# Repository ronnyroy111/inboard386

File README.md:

# Intel Inboard 386/PC Clone
https://forum.vcfed.org/index.php?threads/inboard386-pc-clone.1257894/
https://forum.theretroweb.com/t/intel-inboard-386-pc-accelerator-clone/44

This is a complete reverse engineered reproduction of [Intel Inboard 386/PC Accelerator Card](https://theretroweb.com/expansioncards/s/intel-inboard-386-pc).  
It's based on a damaged card that i obtained a while ago and managed to fix but decided to sacrifice for a reproduction.  
The Inboard 386/PC is an upgrade card from Intel for the IBM PC/XT and clones that upgraded the 8088 CPU to a 16MHz 386DX and up to 5MB of system memory.  
The card only uses standard 74 series logic chips along with some PALs/PROMs that were luckily not secured and were successfully dumped.  
The PCB is a 6 layer design with 4 signal layers. To aid with reverse engineering it i ended up choosing the destructive route and sanded the entire PCB down to the inner layers.  
By now the PCB design has been completed while the schematic still needs cleanup and further reverse engineering of the programmable logic to completely understand.  

The first revision of the board has been tested and confirmed to be working.  
  
Dumps of the PAL Chips and CUPL equations for the replacement Atmel PLD chips are in /logic.  
A memory expansion board prototype can be found under /mem.  
A 3D model of the bracket is at /bracket.  

The original board never intended for more than 5MB of ram to be used but can be modified with updated Logic equations in U71 to theoretically use up to 16MB.  
However the Inboard maps the portion of memory used for ROM caching at 0x580000-5FFFFF which is expected by INBRDPS.SYS.  
Currently that limits >5MB of memory to not use caching but could probably be solved with a modified INBRDPS.SYS.  

This current board design is a 1:1 copy of the original PCB, excluding some small details.  
A more compact version utilising SIMM memory and CPLDs is currently in work.  

# Assembly Guide:
You need the PCB for the inboard as well as the PROM adapter.  
A list of all required other components is located at /inboard386/parts_list.xlsx  
An html BOM is at /inboard386/bom/ibom.html  
The ideal assembly order is to place the small decoupling caps and resistors first, then place the chips and finish with the sockets, headers and large capacitor.  
For bending the capacitors/resistors one of these guides is very useful https://www.thingiverse.com/thing:168412

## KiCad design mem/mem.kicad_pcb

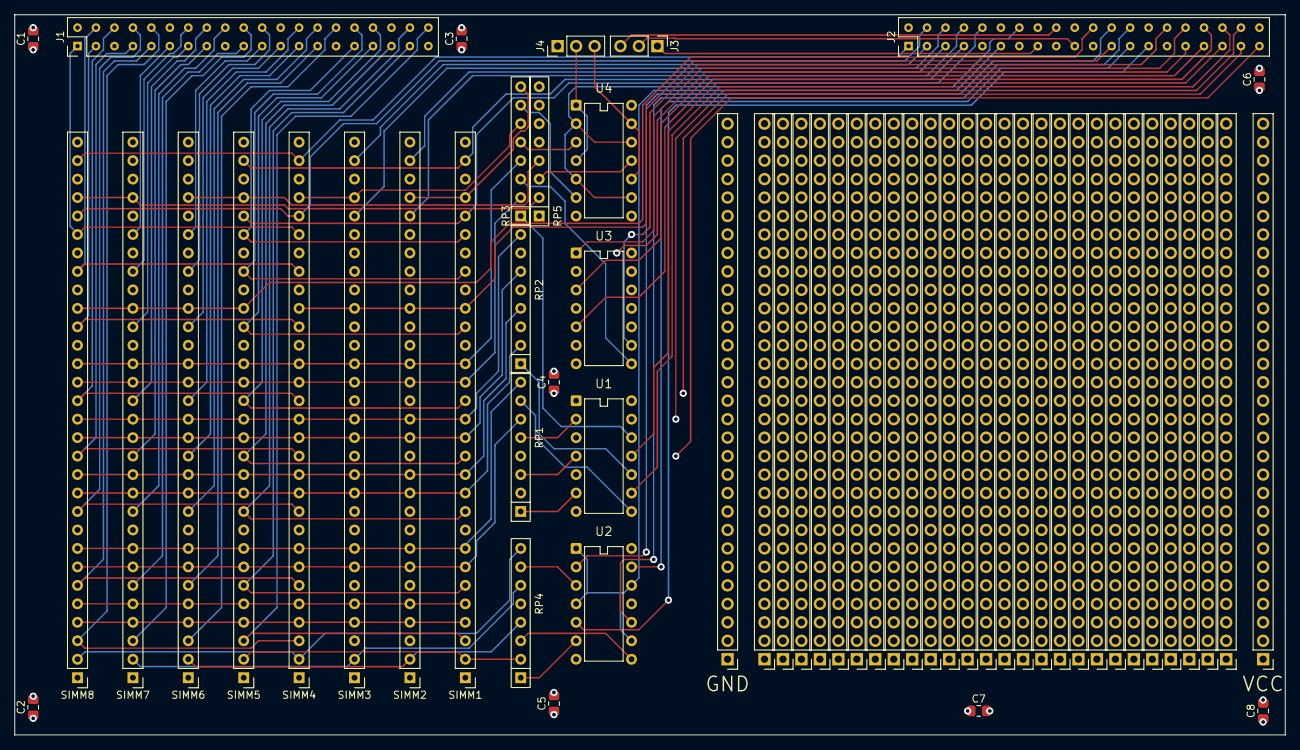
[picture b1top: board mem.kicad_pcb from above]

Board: 4 copper layers, 174.8 x 99.1 mm, 57 parts (0 on the bottom side), 101 nets.

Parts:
C1, C2, C3, C4, C5, C6, C7, C8: 100nF; C_0805_2012Metric_Pad1.18x1.45mm_HandSolder
J1, J2: Conn_02x20_Odd_Even; PinHeader_2x20_P2.54mm_inboard_mem
J3, J4: Conn_01x03_Pin; PinHeader_1x03_P2.54mm_Vertical
J5, J6, J7, J8, J9, J10, J11, J12, J13, J14, J15, J16, J17, J18, J19, J20, J21, J22, J23, J24, J25, J26, J27, J28, J29, J30, J31, J32: Conn_01x30; PinHeader_1x30_P2.54mm_Vertical
RP1, RP2, RP3, RP4, RP5: 22; R_Array_SIP8_layer
SIMM1, SIMM2, SIMM3, SIMM4, SIMM5, SIMM6, SIMM7, SIMM8: SIMM30; PinHeader_1x30_P2.54mm_Vertical_layer
U1, U3: 74AS1004; DIP-14_W7.62mm_layer
U2, U4: 742S1032; DIP-14_W7.62mm_layer

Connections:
+5V: C1.2, C2.2, C3.2, C4.2, C5.2, C6.2, C7.2, C8.2, J1.5, J1.17, J1.29, J1.39, J2.9, J2.13, J2.17, J2.21, J2.29, J30.1, J30.2, J30.3, J30.4, J30.5, J30.6, J30.7, J30.8, J30.9, J30.10, J30.11, J30.12, J30.13, J30.14, J30.15, J30.16, J30.17, J30.18, J30.19, J30.20, J30.21, J30.22, J30.23, J30.24, J30.25, J30.26, J30.27, J30.28, J30.29, J30.30, SIMM1.1 (VCC), SIMM1.30 (VCC), SIMM2.1 (VCC), SIMM2.30 (VCC), SIMM3.1 (VCC), SIMM3.30 (VCC), SIMM4.1 (VCC), SIMM4.30 (VCC), SIMM5.1 (VCC), SIMM5.30 (VCC), SIMM6.1 (VCC), SIMM6.30 (VCC), SIMM7.1 (VCC), SIMM7.30 (VCC), SIMM8.1 (VCC), SIMM8.30 (VCC), U1.14 (VCC), U2.14 (VCC), U3.14 (VCC), U4.14 (VCC)
/RAS_1M: J2.15, J3.1
/RAS_256K_1: J2.19, J3.2
/RAS_256K_2: J2.18, J3.3
GND: C1.1, C2.1, C3.1, C4.1, C5.1, C6.1, C7.1, C8.1, J1.2, J1.12, J1.24, J1.36, J2.2, J2.12, J2.16, J2.20, J2.28, J2.40, J29.1, J29.2, J29.3, J29.4, J29.5, J29.6, J29.7, J29.8, J29.9, J29.10, J29.11, J29.12, J29.13, J29.14, J29.15, J29.16, J29.17, J29.18, J29.19, J29.20, J29.21, J29.22, J29.23, J29.24, J29.25, J29.26, J29.27, J29.28, J29.29, J29.30, SIMM1.9 (GND), SIMM1.22 (GND), SIMM2.9 (GND), SIMM2.22 (GND), SIMM3.9 (GND), SIMM3.22 (GND), SIMM4.9 (GND), SIMM4.22 (GND), SIMM5.9 (GND), SIMM5.22 (GND), SIMM6.9 (GND), SIMM6.22 (GND), SIMM7.9 (GND), SIMM7.22 (GND), SIMM8.9 (GND), SIMM8.22 (GND), U1.7 (GND), U2.7 (GND), U3.7 (GND), U4.7 (GND)
MA0: RP1.2 (R1.2), SIMM1.4 (A0), SIMM2.4 (A0), SIMM3.4 (A0), SIMM4.4 (A0), SIMM5.4 (A0), SIMM6.4 (A0), SIMM7.4 (A0), SIMM8.4 (A0)
MA1: RP1.4 (R2.2), SIMM1.5 (A1), SIMM2.5 (A1), SIMM3.5 (A1), SIMM4.5 (A1), SIMM5.5 (A1), SIMM6.5 (A1), SIMM7.5 (A1), SIMM8.5 (A1)
MA2: RP1.6 (R3.2), SIMM1.7 (A2), SIMM2.7 (A2), SIMM3.7 (A2), SIMM4.7 (A2), SIMM5.7 (A2), SIMM6.7 (A2), SIMM7.7 (A2), SIMM8.7 (A2)
MA3: RP1.8 (R4.2), SIMM1.8 (A3), SIMM2.8 (A3), SIMM3.8 (A3), SIMM4.8 (A3), SIMM5.8 (A3), SIMM6.8 (A3), SIMM7.8 (A3), SIMM8.8 (A3)
MA4: RP2.2 (R1.2), SIMM1.11 (A4), SIMM2.11 (A4), SIMM3.11 (A4), SIMM4.11 (A4), SIMM5.11 (A4), SIMM6.11 (A4), SIMM7.11 (A4), SIMM8.11 (A4)
MA5: RP2.4 (R2.2), SIMM1.12 (A5), SIMM2.12 (A5), SIMM3.12 (A5), SIMM4.12 (A5), SIMM5.12 (A5), SIMM6.12 (A5), SIMM7.12 (A5), SIMM8.12 (A5)
MA6: RP2.6 (R3.2), SIMM1.14 (A6), SIMM2.14 (A6), SIMM3.14 (A6), SIMM4.14 (A6), SIMM5.14 (A6), SIMM6.14 (A6), SIMM7.14 (A6), SIMM8.14 (A6)
MA7: RP2.8 (R4.2), SIMM1.15 (A7), SIMM2.15 (A7), SIMM3.15 (A7), SIMM4.15 (A7), SIMM5.15 (A7), SIMM6.15 (A7), SIMM7.15 (A7), SIMM8.15 (A7)
MA8: RP3.2 (R1.2), SIMM1.17 (A8), SIMM2.17 (A8), SIMM3.17 (A8), SIMM4.17 (A8), SIMM5.17 (A8), SIMM6.17 (A8), SIMM7.17 (A8), SIMM8.17 (A8)
MA9: RP3.4 (R2.2), SIMM1.18 (A9), SIMM2.18 (A9), SIMM3.18 (A9), SIMM4.18 (A9), SIMM5.18 (A9), SIMM6.18 (A9), SIMM7.18 (A9), SIMM8.18 (A9)
MBE0: J2.27, U2.5
MBE1: J2.26, U2.10
MBE2: J2.25, U2.13
MBE3: J2.24, U2.2
MD0: J1.40, SIMM1.3 (D0), SIMM5.3 (D0)
MD1: J1.37, SIMM1.6 (D1), SIMM5.6 (D1)
MD2: J1.38, SIMM1.10 (D2), SIMM5.10 (D2)
MD3: J1.35, SIMM1.13 (D3), SIMM5.13 (D3)
MD4: J1.34, SIMM1.16 (D4), SIMM5.16 (D4)
MD5: J1.33, SIMM1.20 (D5), SIMM5.20 (D5)
MD6: J1.32, SIMM1.23 (D6), SIMM5.23 (D6)
MD7: J1.31, SIMM1.25 (D7), SIMM5.25 (D7)
MD8: J1.30, SIMM2.3 (D0), SIMM6.3 (D0)
MD9: J1.27, SIMM2.6 (D1), SIMM6.6 (D1)
MD10: J1.28, SIMM2.10 (D2), SIMM6.10 (D2)
MD11: J1.25, SIMM2.13 (D3), SIMM6.13 (D3)
MD12: J1.26, SIMM2.16 (D4), SIMM6.16 (D4)
MD13: J1.23, SIMM2.20 (D5), SIMM6.20 (D5)
MD14: J1.22, SIMM2.23 (D6), SIMM6.23 (D6)
MD15: J1.21, SIMM2.25 (D7), SIMM6.25 (D7)
MD16: J1.20, SIMM3.3 (D0), SIMM7.3 (D0)
MD17: J1.19, SIMM3.6 (D1), SIMM7.6 (D1)
MD18: J1.18, SIMM3.10 (D2), SIMM7.10 (D2)
MD19: J1.15, SIMM3.13 (D3), SIMM7.13 (D3)
MD20: J1.16, SIMM3.16 (D4), SIMM7.16 (D4)
MD21: J1.13, SIMM3.20 (D5), SIMM7.20 (D5)
MD22: J1.14, SIMM3.23 (D6), SIMM7.23 (D6)
MD23: J1.11, SIMM3.25 (D7), SIMM7.25 (D7)
MD24: J1.10, SIMM4.3 (D0), SIMM8.3 (D0)
MD25: J1.9, SIMM4.6 (D1), SIMM8.6 (D1)
MD26: J1.8, SIMM4.10 (D2), SIMM8.10 (D2)
MD27: J1.7, SIMM4.13 (D3), SIMM8.13 (D3)
MD28: J1.6, SIMM4.16 (D4), SIMM8.16 (D4)
MD29: J1.3, SIMM4.20 (D5), SIMM8.20 (D5)
MD30: J1.4, SIMM4.23 (D6), SIMM8.23 (D6)
MD31: J1.1, SIMM4.25 (D7), SIMM8.25 (D7)
MP0: J2.10, SIMM1.26 (P-OUT), SIMM5.26 (P-OUT)
MP0IN: J2.7, SIMM1.29 (P-IN), SIMM5.29 (P-IN)
MP1: J2.8, SIMM2.26 (P-OUT), SIMM6.26 (P-OUT)
MP1IN: J2.5, SIMM2.29 (P-IN), SIMM6.29 (P-IN)
MP2: J2.6, SIMM3.26 (P-OUT), SIMM7.26 (P-OUT)
MP2IN: J2.3, SIMM3.29 (P-IN), SIMM7.29 (P-IN)
MP3: J2.4, SIMM4.26 (P-OUT), SIMM8.26 (P-OUT)
MP3IN: J2.1, SIMM4.29 (P-IN), SIMM8.29 (P-IN)
unnamed: J4.2, U4.1, U4.4
unnamed: J4.3, U4.10, U4.13
unnamed: RP1.1 (R1.1), U1.6
unnamed: RP1.3 (R2.1), U1.4
unnamed: RP1.5 (R3.1), U1.2
unnamed: RP1.7 (R4.1), U1.8
unnamed: RP2.1 (R1.1), U1.10
unnamed: RP2.3 (R2.1), U3.6
unnamed: RP2.5 (R3.1), U3.4
unnamed: RP2.7 (R4.1), U3.2
unnamed: RP3.1 (R1.1), U1.12
unnamed: RP3.3 (R2.1), U3.8
unnamed: RP3.5 (R3.1), U4.3
unnamed: RP3.7 (R4.1), U4.6
unnamed: RP4.1 (R1.1), U2.6
unnamed: RP4.3 (R2.1), U2.8
unnamed: RP4.5 (R3.1), U2.11
unnamed: RP4.7 (R4.1), U2.3
unnamed: RP5.1 (R1.1), U4.8
unnamed: RP5.3 (R2.1), U4.11
~CAS0: RP4.2 (R1.2), SIMM1.2 (~CAS), SIMM1.28 (CASP), SIMM5.2 (~CAS), SIMM5.28 (CASP)
~CAS1: RP4.4 (R2.2), SIMM2.2 (~CAS), SIMM2.28 (CASP), SIMM6.2 (~CAS), SIMM6.28 (CASP)
~CAS2: RP4.6 (R3.2), SIMM3.2 (~CAS), SIMM3.28 (CASP), SIMM7.2 (~CAS), SIMM7.28 (CASP)
~CAS3: RP4.8 (R4.2), SIMM4.2 (~CAS), SIMM4.28 (CASP), SIMM8.2 (~CAS), SIMM8.28 (CASP)
~CAS: J2.11, U2.1, U2.4, U2.9, U2.12
~MA0: J2.39, U1.5
~MA1: J2.38, U1.3
~MA2: J2.37, U1.1
~MA3: J2.36, U1.9
~MA4: J2.35, U1.11
~MA5: J2.34, U3.5
~MA6: J2.33, U3.3
~MA7: J2.32, U3.1
~MA8: J2.31, U1.13
~MA9?: J2.30, U3.9
~MEMW_E0: J2.23, SIMM1.21 (~WE), SIMM2.21 (~WE), SIMM3.21 (~WE), SIMM4.21 (~WE)
~MEMW_E1: J2.22, SIMM5.21 (~WE), SIMM6.21 (~WE), SIMM7.21 (~WE), SIMM8.21 (~WE)
~RAS?: J2.14, U4.2, U4.5, U4.9, U4.12
~RASH_0: RP3.6 (R3.2), SIMM3.27 (~RAS), SIMM4.27 (~RAS)
~RASH_1: RP5.2 (R1.2), SIMM7.27 (~RAS), SIMM8.27 (~RAS)
~RASL_0: RP3.8 (R4.2), SIMM1.27 (~RAS), SIMM2.27 (~RAS)
~RASL_1: RP5.4 (R2.2), SIMM5.27 (~RAS), SIMM6.27 (~RAS)

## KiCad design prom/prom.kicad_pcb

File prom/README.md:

A small adapter PCB to replace the 63S281 PROM at U98 with a modern PLCC EEPROM.

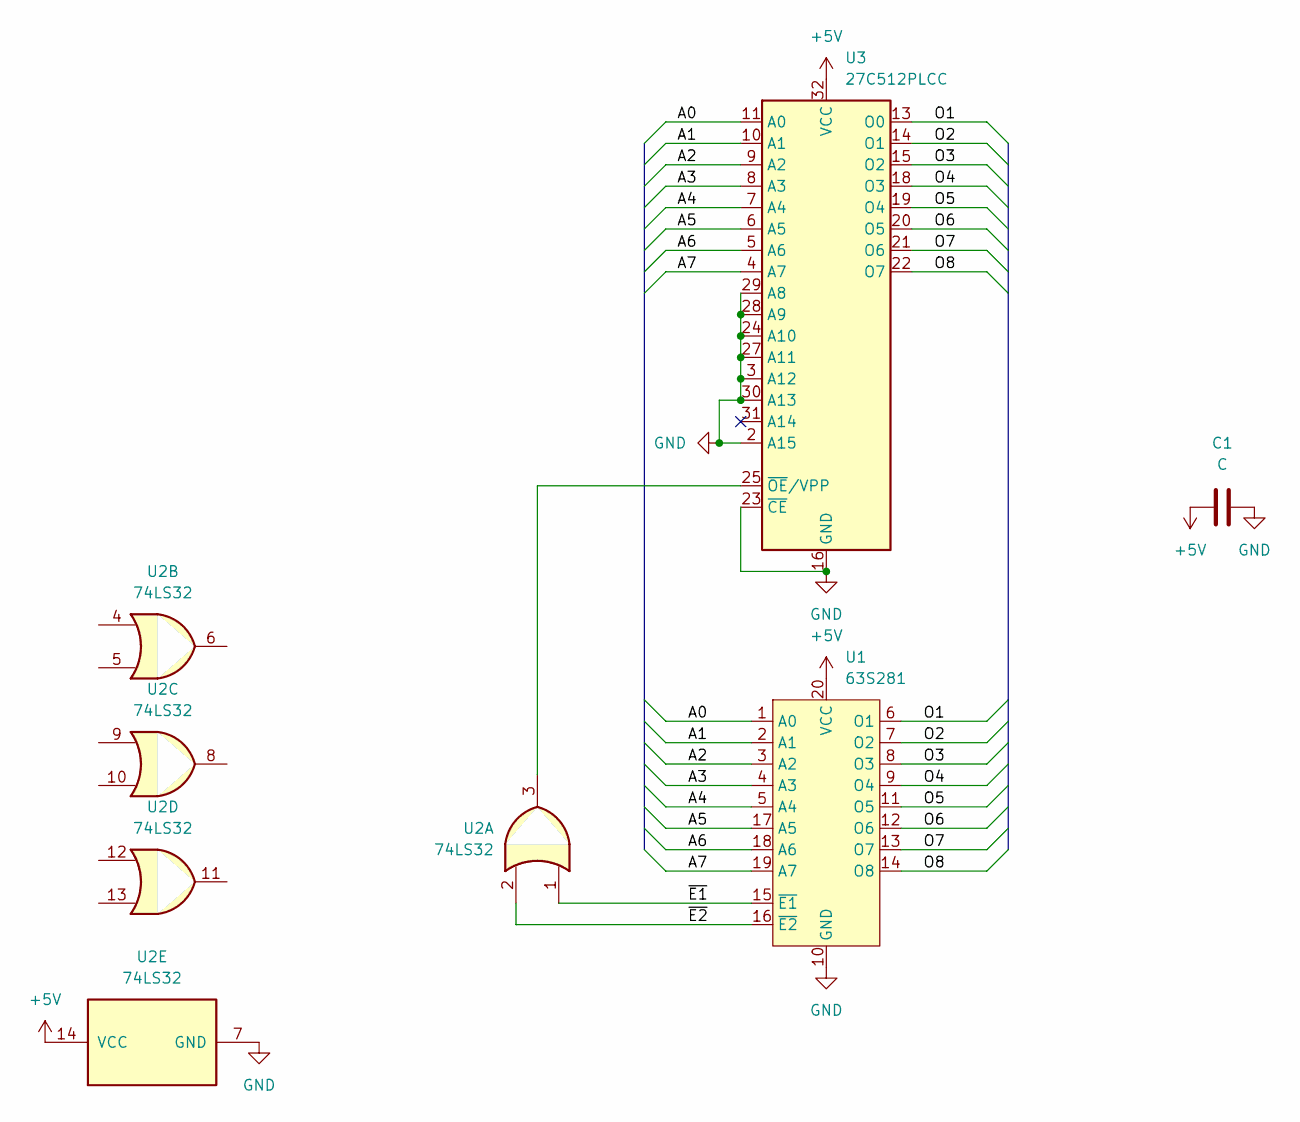
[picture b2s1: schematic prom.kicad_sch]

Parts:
C1: C; C_0805_2012Metric_Pad1.18x1.45mm_HandSolder
U1: 63S281; DIP-20_W7.62mm
U2: 74LS32; SOIC-14_3.9x8.7mm_P1.27mm
U3: 27C512PLCC; PLCC-32_11.4x14.0mm_P1.27mm

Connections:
+5V: C1.1, U1.20 (VCC), U2.14 (VCC), U3.32 (VCC)
/A0: U1.1 (A0), U3.11 (A0)
/A1: U1.2 (A1), U3.10 (A1)
/A2: U1.3 (A2), U3.9 (A2)
/A3: U1.4 (A3), U3.8 (A3)
/A4: U1.5 (A4), U3.7 (A4)
/A5: U1.17 (A5), U3.6 (A5)
/A6: U1.18 (A6), U3.5 (A6)
/A7: U1.19 (A7), U3.4 (A7)
/O1: U1.6 (O1), U3.13 (O0)
/O2: U1.7 (O2), U3.14 (O1)
/O3: U1.8 (O3), U3.15 (O2)
/O4: U1.9 (O4), U3.18 (O3)
/O5: U1.11 (O5), U3.19 (O4)
/O6: U1.12 (O6), U3.20 (O5)
/O7: U1.13 (O7), U3.21 (O6)
/O8: U1.14 (O8), U3.22 (O7)
/~E1: U1.15 (~E1), U2.1
/~E2: U1.16 (~E2), U2.2
GND: C1.2, U1.10 (GND), U2.7 (GND), U3.2 (A15), U3.3 (A12), U3.16 (GND), U3.23 (~CE), U3.24 (A10), U3.27 (A11), U3.28 (A9), U3.29 (A8), U3.30 (A13)
unnamed: U2.3, U3.25 (~OE/VPP)

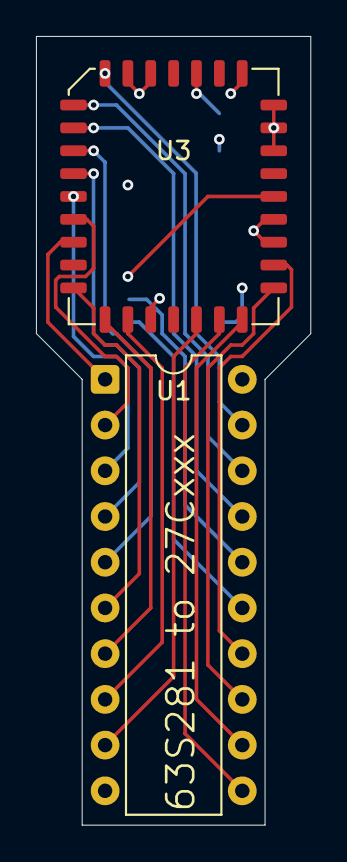
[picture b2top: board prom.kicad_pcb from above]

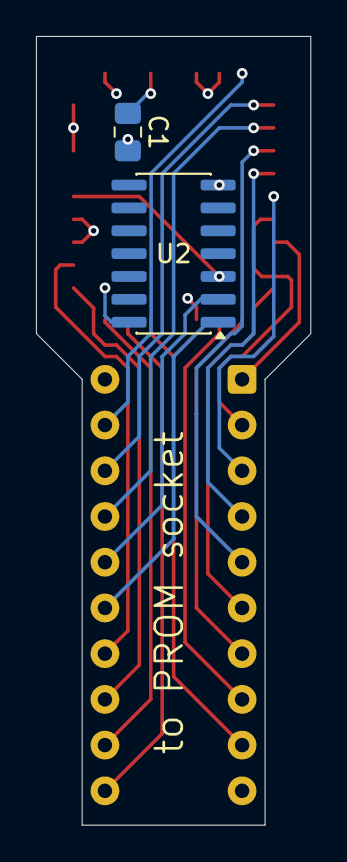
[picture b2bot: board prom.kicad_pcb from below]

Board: 4 copper layers, 15.2 x 43.8 mm, 4 parts (2 on the bottom side), 21 nets.

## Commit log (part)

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2026-05-24 Initial project commit. PCB design rev. 0.1
2026-05-24 Add README
    Added project details for Intel Inboard 386/PC Clone including reverse engineering efforts and future plans.
2026-05-24 Fix typo in README.md
2026-05-24 Add README for PROM adapter
2026-05-24 Add raw PAL dumps and extracted logic equations
2026-05-24 update README, add images
2026-05-24 update image
2026-06-13 minimal updates to schematic labelling
2026-06-13 Add CUPL code and compiled jed files.
2026-06-13 Add pictures of assmebled and running board
2026-06-13 fix image scaling
2026-06-13 Update README with board images and project status
2026-06-16 Add MIT License to the project
2026-06-16 Add parts list spreadsheet
2026-06-16 Add PROM adapter components to parts list
